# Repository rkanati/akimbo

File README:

work in progress, watch this space

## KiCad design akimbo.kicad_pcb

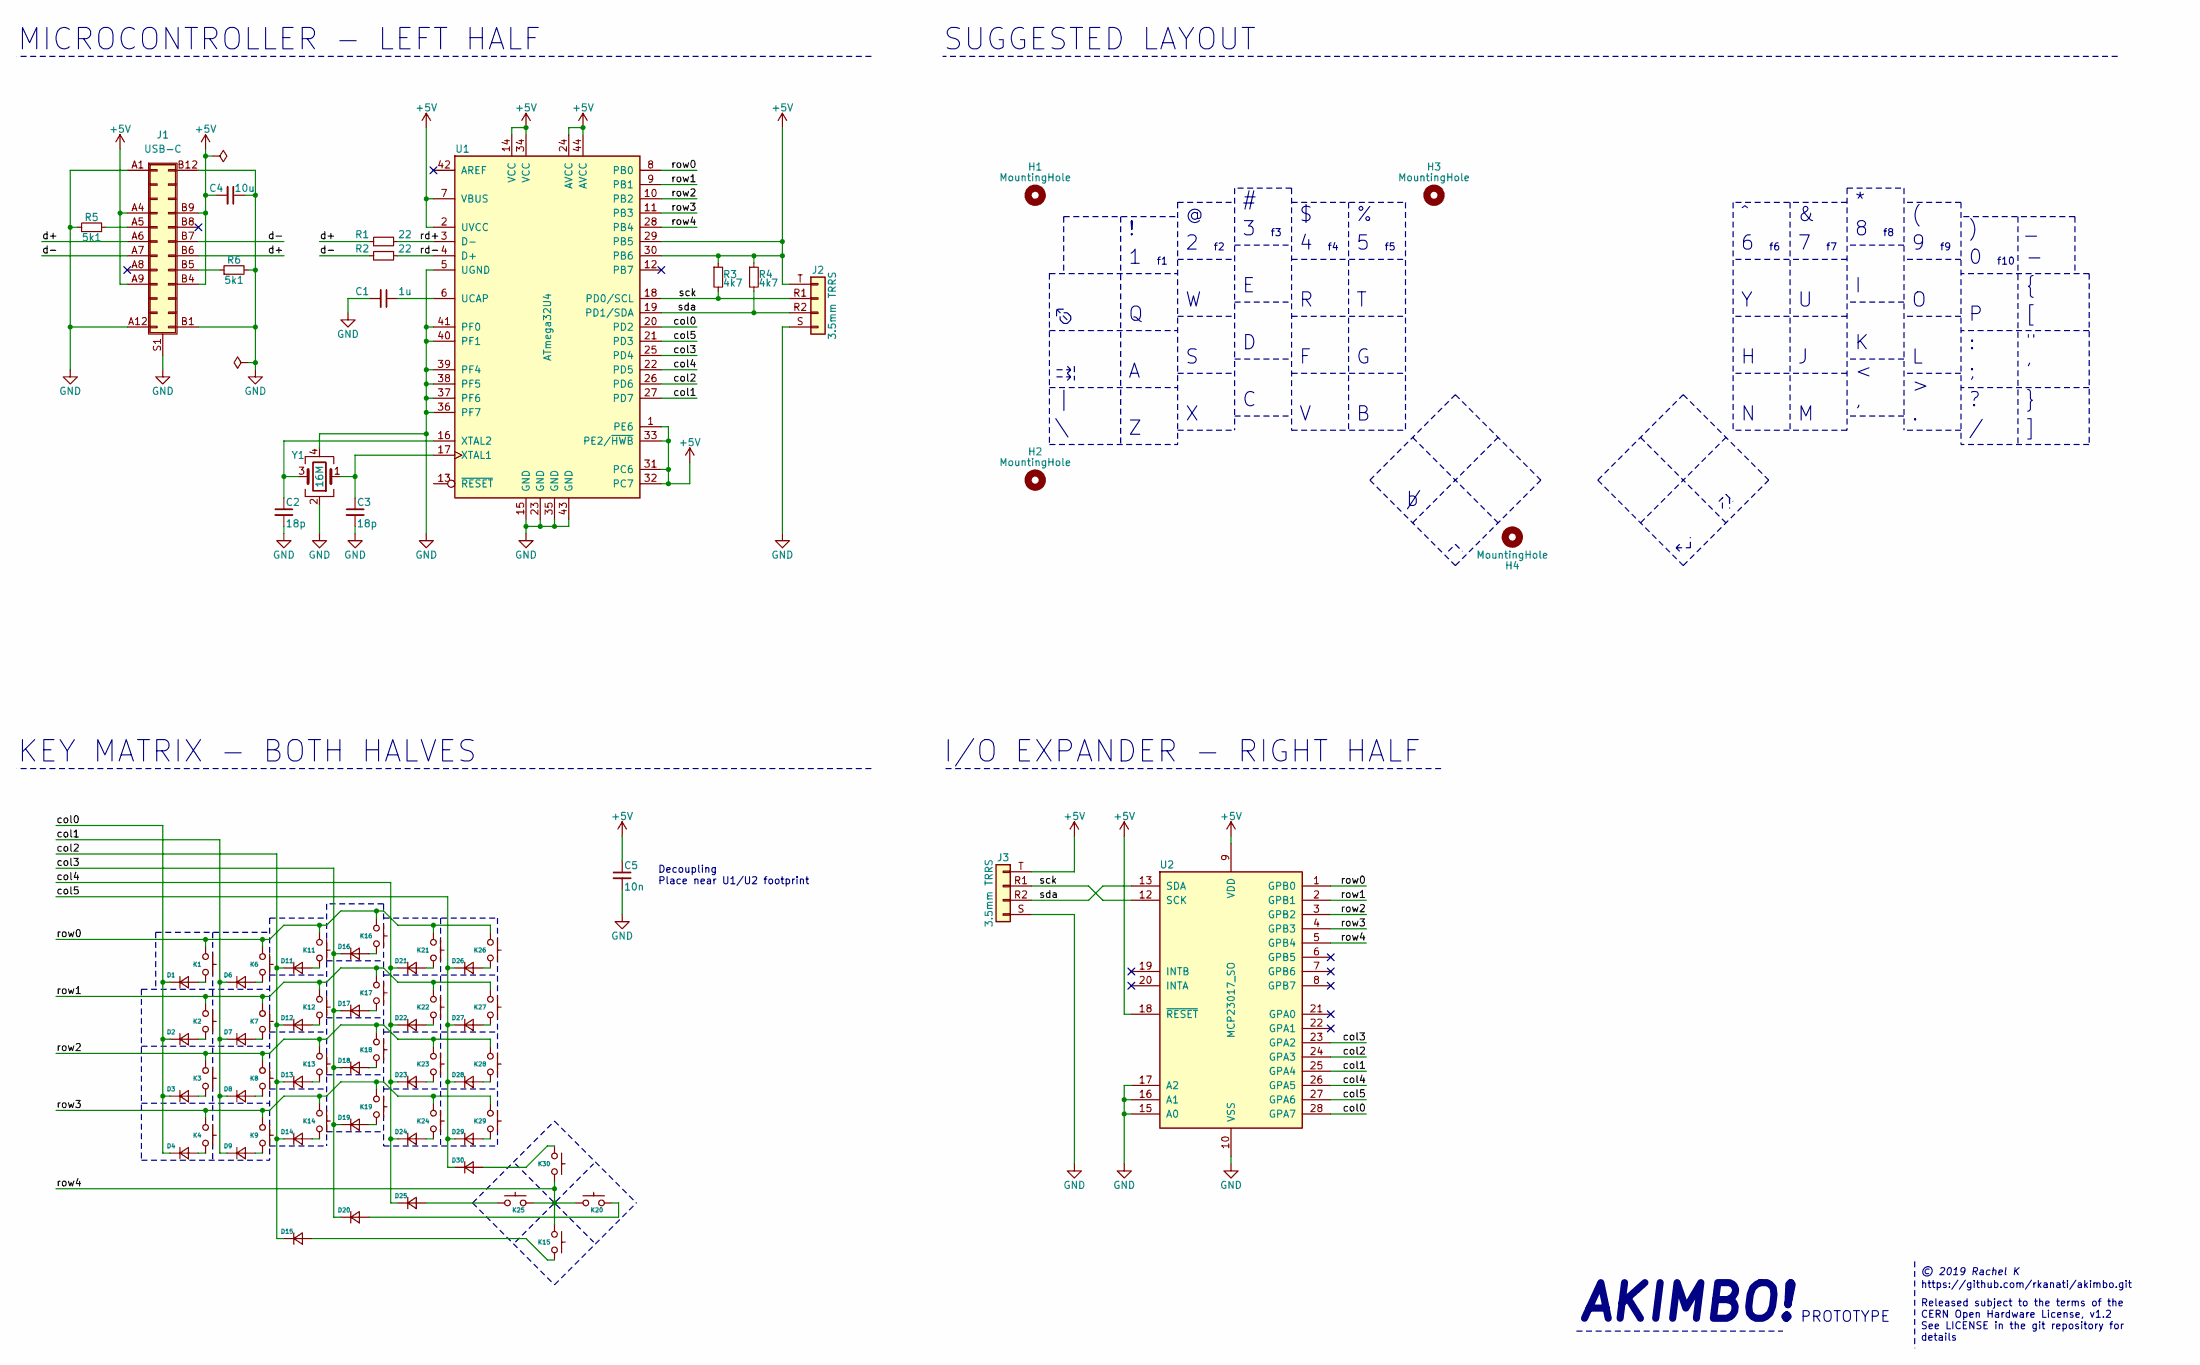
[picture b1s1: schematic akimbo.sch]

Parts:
C1: 1u; C_0805_2012Metric_Pad1.15x1.40mm_HandSolder
C2, C3: 18p; C_0805_2012Metric_Pad1.15x1.40mm_HandSolder
C4: 10u; C_0805_2012Metric_Pad1.15x1.40mm_HandSolder
C5: 10n; C_0805_2012Metric_Pad1.15x1.40mm_HandSolder
D1, D2, D3, D4, D6, D7, D8, D9, D11, D12, D13, D14, D15, D16, D17, D18, D19, D20, D21, D22, D23, D24, D25, D26, D27, D28, D29, D30: D_Small; D_DO-35_SOD27_P7.62mm_Horizontal
H1, H2, H3, H4: MountingHole; MountingHole_3.2mm_M3
J1: USB-C; USB_C_Receptacle_GCT_USB4085
J2, J3: 3.5mm TRRS; Jack_3.5mm_PJ320D_Horizontal
K1, K2, K3, K4, K6, K7, K8, K9, K11, K12, K13, K14, K15, K16, K17, K18, K19, K20, K21, K22, K23, K24, K25, K26, K27, K28, K29, K30: -; SW_Cherry_MX_1.00u_PCB_Reversible
R1, R2: 22; R_0805_2012Metric_Pad1.15x1.40mm_HandSolder
R3, R4: 4k7; R_0805_2012Metric_Pad1.15x1.40mm_HandSolder
R5, R6: 5k1; R_0805_2012Metric_Pad1.15x1.40mm_HandSolder
U1: ATmega32U4; TQFP-44_10x10mm_P0.8mm
U2: MCP23017_SO; SOIC-28W_7.5x17.9mm_P1.27mm
Y1: 16M; Crystal_SMD_3225-4Pin_3.2x2.5mm_HandSoldering

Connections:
+5V: C4.2, C5.1, J1.A4, J1.A9, J1.B4, J1.B9, J2.T, J3.T, R3.1, R4.1, U1.1 (PE6), U1.2 (UVCC), U1.7 (VBUS), U1.14 (VCC), U1.24 (AVCC), U1.29 (PB5), U1.30 (PB6), U1.31 (PC6), U1.32 (PC7), U1.33 (PE2/~HWB), U1.34 (VCC), U1.44 (AVCC), U2.9 (VDD), U2.18 (~RESET~)
/col0: D1.1 (K), D2.1 (K), D3.1 (K), D4.1 (K), U1.20 (PD2), U2.28 (GPA7)
/col1: D6.1 (K), D7.1 (K), D8.1 (K), D9.1 (K), U1.27 (PD7), U2.25 (GPA4)
/col2: D11.1 (K), D12.1 (K), D13.1 (K), D14.1 (K), D15.1 (K), U1.26 (PD6), U2.24 (GPA3)
/col3: D16.1 (K), D17.1 (K), D18.1 (K), D19.1 (K), D20.1 (K), U1.25 (PD4), U2.23 (GPA2)
/col4: D21.1 (K), D22.1 (K), D23.1 (K), D24.1 (K), D25.1 (K), U1.22 (PD5), U2.26 (GPA5)
/col5: D26.1 (K), D27.1 (K), D28.1 (K), D29.1 (K), D30.1 (K), U1.21 (PD3), U2.27 (GPA6)
/d+: J1.A6, J1.B6, R1.2
/d-: J1.A7, J1.B7, R2.2
/rd+: R1.1, U1.3 (D-)
/rd-: R2.1, U1.4 (D+)
/row0: K1.1, K6.1, K11.1, K16.1, K21.1, K26.1, U1.8 (PB0), U2.1 (GPB0)
/row1: K2.1, K7.1, K12.1, K17.1, K22.1, K27.1, U1.9 (PB1), U2.2 (GPB1)
/row2: K3.1, K8.1, K13.1, K18.1, K23.1, K28.1, U1.10 (PB2), U2.3 (GPB2)
/row3: K4.1, K9.1, K14.1, K19.1, K24.1, K29.1, U1.11 (PB3), U2.4 (GPB3)
/row4: K15.2, K20.1, K25.1, K30.2, U1.28 (PB4), U2.5 (GPB4)
/sck: J2.R1, J3.R1, R3.2, U1.18 (PD0/SCL), U2.12 (SCK)
/sda: J2.R2, J3.R2, R4.2, U1.19 (PD1/SDA), U2.13 (SDA)
GND: C1.2, C2.2, C3.2, C4.1, C5.2, J1.A1, J1.A12, J1.B1, J1.B12, J1.S1 (Shield), J2.S, J3.S, R5.1, R6.2, U1.5 (UGND), U1.15 (GND), U1.23 (GND), U1.35 (GND), U1.36 (PF7), U1.37 (PF6), U1.38 (PF5), U1.39 (PF4), U1.40 (PF1), U1.41 (PF0), U1.43 (GND), U2.10 (VSS), U2.15 (A0), U2.16 (A1), U2.17 (A2), Y1.2, Y1.4
unnamed: C1.1, U1.6 (UCAP)
unnamed: C2.1, U1.16 (XTAL2), Y1.3
unnamed: C3.1, U1.17 (XTAL1), Y1.1
unnamed: D1.2 (A), K1.2
unnamed: D2.2 (A), K2.2
unnamed: D3.2 (A), K3.2
unnamed: D4.2 (A), K4.2
unnamed: D6.2 (A), K6.2
unnamed: D7.2 (A), K7.2
unnamed: D8.2 (A), K8.2
unnamed: D9.2 (A), K9.2
unnamed: D11.2 (A), K11.2
unnamed: D12.2 (A), K12.2
unnamed: D13.2 (A), K13.2
unnamed: D14.2 (A), K14.2
unnamed: D15.2 (A), K15.1
unnamed: D16.2 (A), K16.2
unnamed: D17.2 (A), K17.2
unnamed: D18.2 (A), K18.2
unnamed: D19.2 (A), K19.2
unnamed: D20.2 (A), K20.2
unnamed: D21.2 (A), K21.2
unnamed: D22.2 (A), K22.2
unnamed: D23.2 (A), K23.2
unnamed: D24.2 (A), K24.2
unnamed: D25.2 (A), K25.2
unnamed: D26.2 (A), K26.2
unnamed: D27.2 (A), K27.2
unnamed: D28.2 (A), K28.2
unnamed: D29.2 (A), K29.2
unnamed: D30.2 (A), K30.1
unnamed: J1.A5, R5.2
unnamed: J1.B5, R6.1

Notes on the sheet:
f10
AKIMBO!
PROTOTYPE
Released subject to the terms of the CERN Open Hardware License, v1.2 See LICENSE in the git repository for details
MICROCONTROLLER - LEFT HALF
KEY MATRIX - BOTH HALVES
I/O EXPANDER - RIGHT HALF
SUGGESTED LAYOUT
Decoupling Place near U1/U2 footprint
https://github.com/rkanati/akimbo.git
© 2019 Rachel K

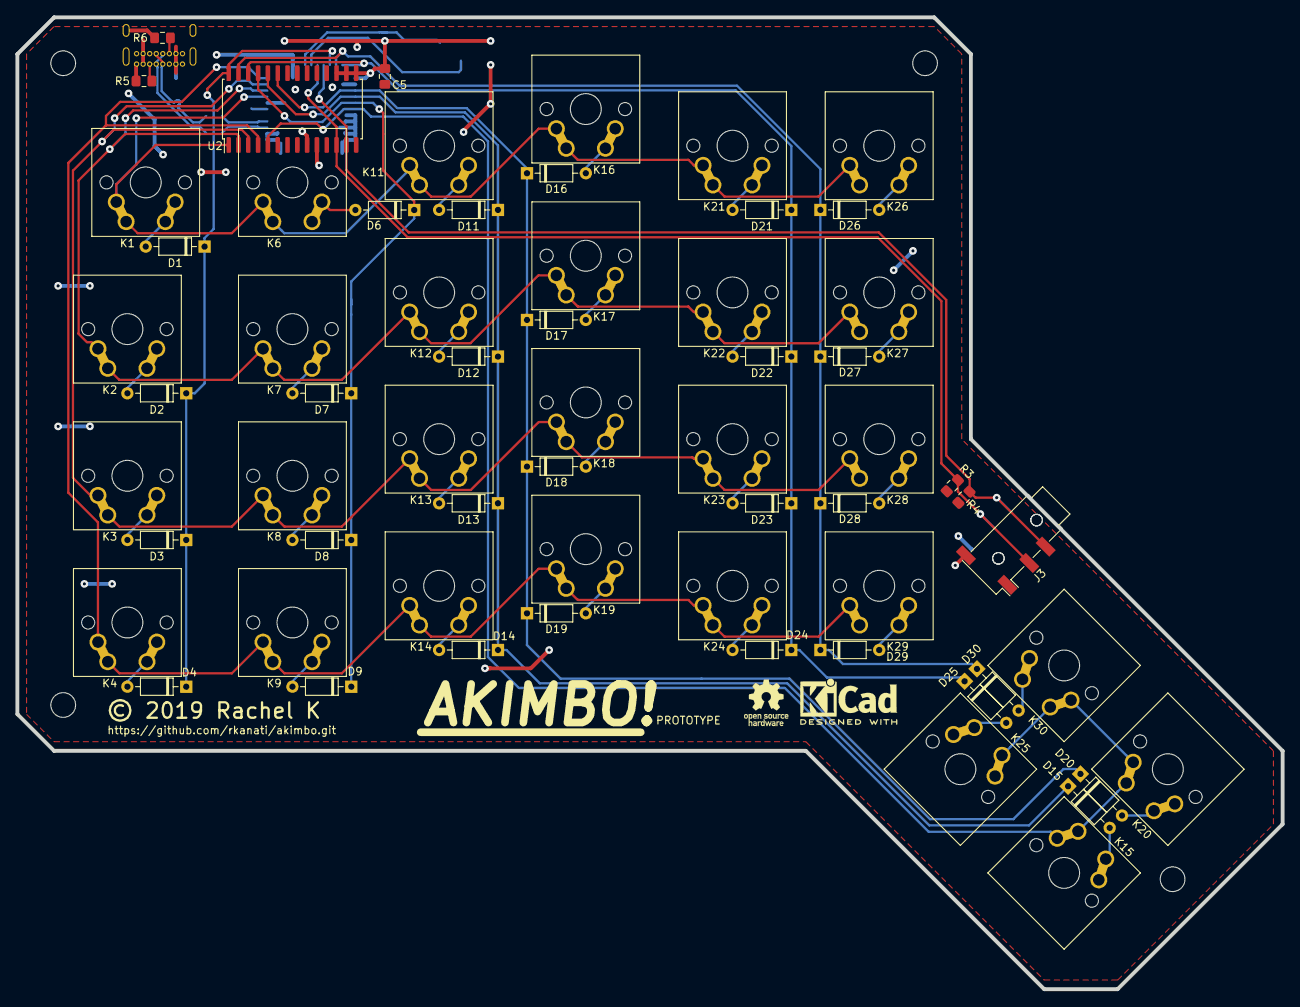
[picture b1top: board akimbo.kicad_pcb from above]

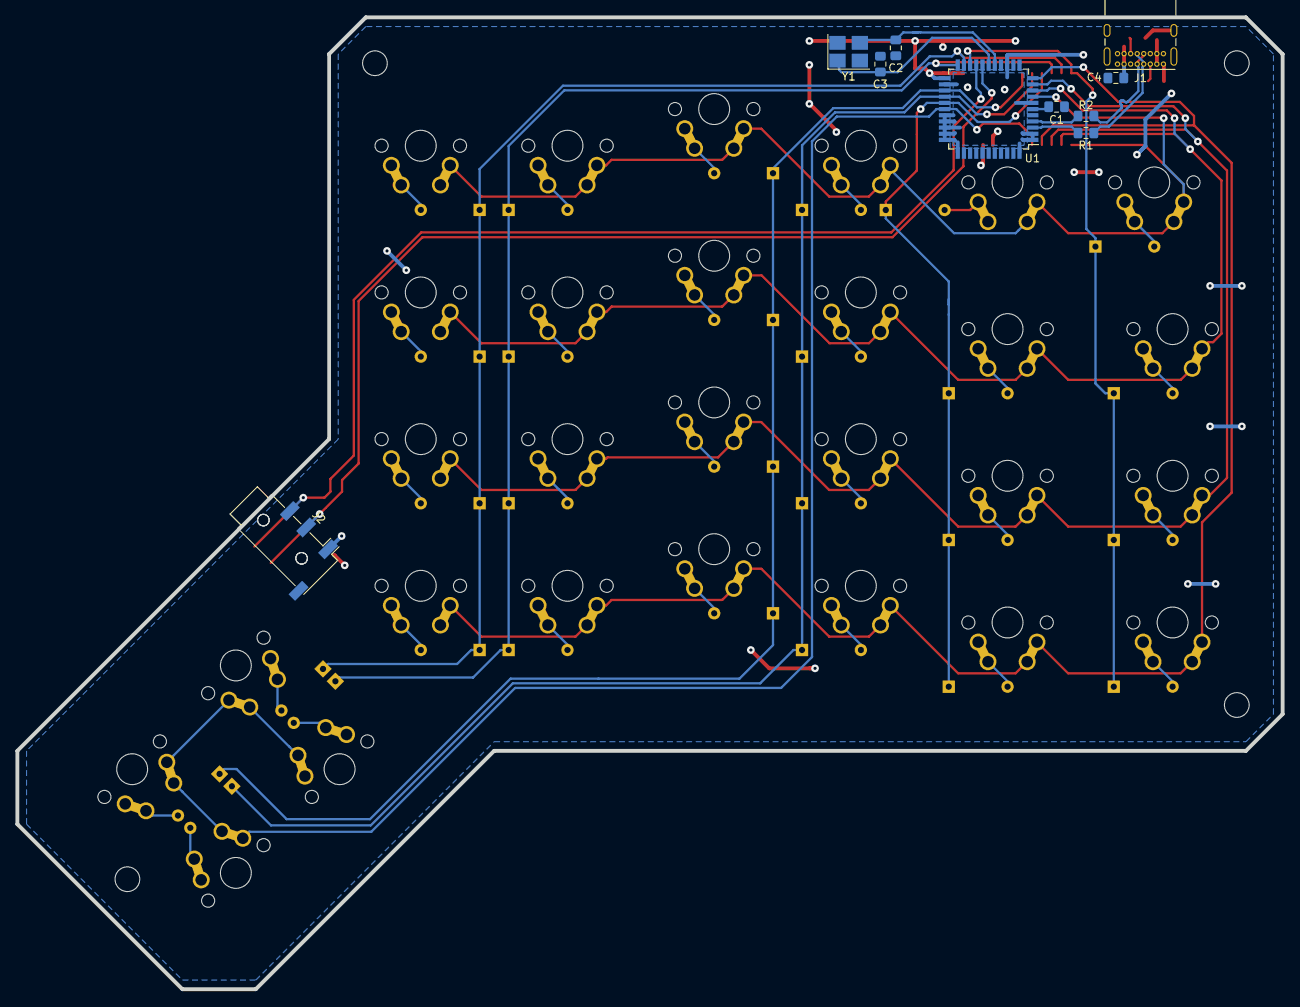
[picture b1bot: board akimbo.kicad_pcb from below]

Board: 2 copper layers, 163.9 x 125.9 mm, 77 parts (10 on the bottom side), 52 nets.

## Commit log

2019-08-28 started BOM
2019-08-29 I2C pullups
2019-08-29 Tweaked silkscreen; routing tweaks; cleanup
2019-08-29 replace mcp23017 with pca9995
2019-08-29 USB-C instead of mini-B
2019-08-29 silkscreen position fixes
2019-08-29 silkscreen cleanup
2019-08-29 I2C routing improvements
    avoids running sda/sck too close to the crystal oscillator
2019-08-29 schematic cleanup, BOM essentially complete
2019-08-30 decoupling caps; better crystal-μC routing
2019-08-30 minor tweaks, no functional changes
